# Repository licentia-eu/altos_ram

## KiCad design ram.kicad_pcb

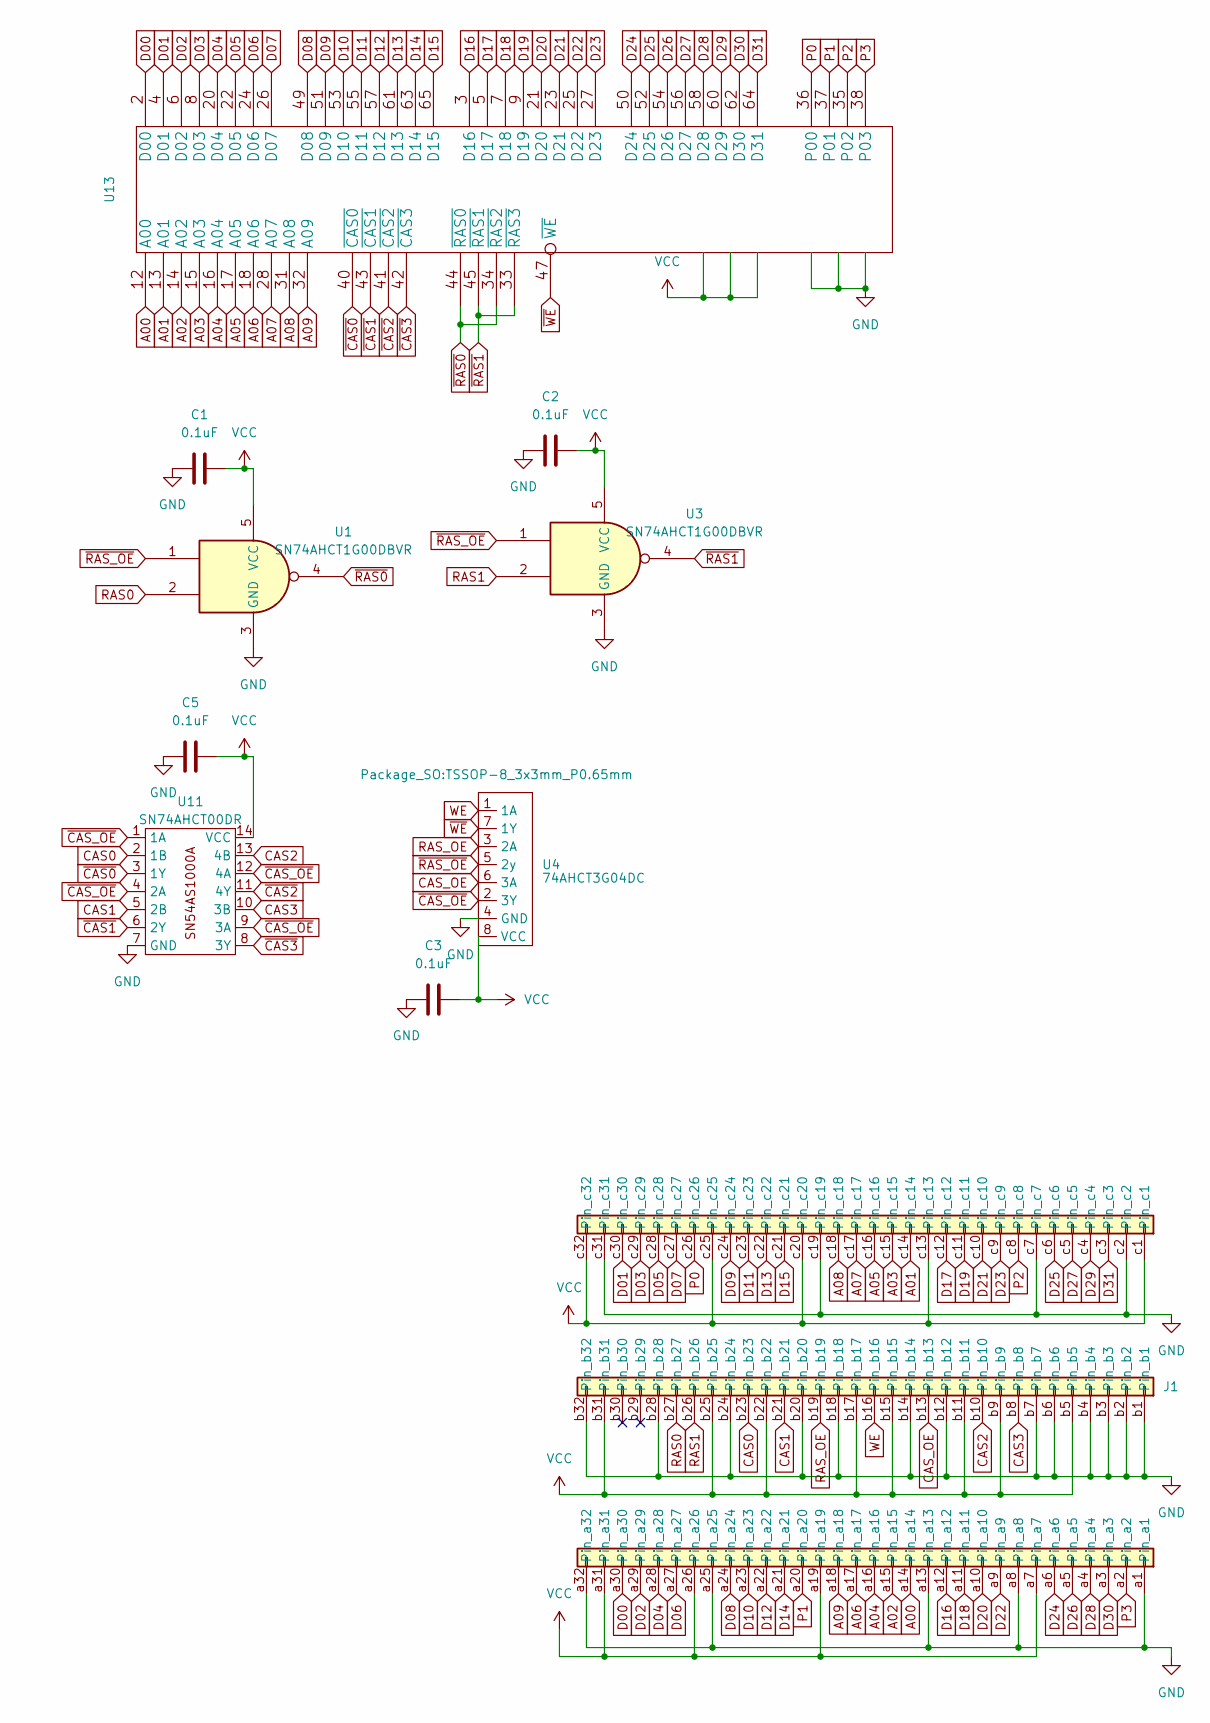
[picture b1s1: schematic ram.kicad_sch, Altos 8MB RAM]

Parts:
C1, C2, C3, C5: 0.1uF; C_1210_3225Metric
J1: DIN41612_R_3x32_Male_Horizontal_THT
U1, U3: SN74AHCT1G00DBVR; SOT-23-5
U4: 74AHCT3G04DC; TSSOP-8_3x3mm_P0.65mm
U11: SN74AHCT00DR; SSOP-14_5.3x6.2mm_P0.65mm
U13: SIM72

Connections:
A00: J1.a14, U13.12 (A00)
A01: J1.c14, U13.13 (A01)
A02: J1.a15, U13.14 (A02)
A03: J1.c15, U13.15 (A03)
A04: J1.a16, U13.16 (A04)
A05: J1.c16, U13.17 (A05)
A06: J1.a17, U13.18 (A06)
A07: J1.c17, U13.28 (A07)
A08: J1.c18, U13.31 (A08)
A09: J1.a18, U13.32 (A09)
CAS0: J1.b23, U11.2 (1B)
CAS1: J1.b21, U11.5 (2B)
CAS2: J1.b10, U11.13 (4B)
CAS3: J1.b8, U11.10 (3B)
CAS_OE: J1.b13, U4.6 (3A)
D00: J1.a30, U13.2 (D00)
D01: J1.c30, U13.4 (D01)
D02: J1.a29, U13.6 (D02)
D03: J1.c29, U13.8 (D03)
D04: J1.a28, U13.20 (D04)
D05: J1.c28, U13.22 (D05)
D06: J1.a27, U13.24 (D06)
D07: J1.c27, U13.26 (D07)
D08: J1.a24, U13.49 (D08)
D09: J1.c24, U13.51 (D09)
D10: J1.a23, U13.53 (D10)
D11: J1.c23, U13.55 (D11)
D12: J1.a22, U13.57 (D12)
D13: J1.c22, U13.61 (D13)
D14: J1.a21, U13.63 (D14)
D15: J1.c21, U13.65 (D15)
D16: J1.a12, U13.3 (D16)
D17: J1.c12, U13.5 (D17)
D18: J1.a11, U13.7 (D18)
D19: J1.c11, U13.9 (D19)
D20: J1.a10, U13.21 (D20)
D21: J1.c10, U13.23 (D21)
D22: J1.a9, U13.25 (D22)
D23: J1.c9, U13.27 (D23)
D24: J1.a6, U13.50 (D24)
D25: J1.c6, U13.52 (D25)
D26: J1.a5, U13.54 (D26)
D27: J1.c5, U13.56 (D27)
D28: J1.a4, U13.58 (D28)
D29: J1.c4, U13.60 (D29)
D30: J1.a3, U13.62 (D30)
D31: J1.c3, U13.64 (D31)
GND: C1.1, C2.1, C3.1, C5.1, J1.a1, J1.a8, J1.a13, J1.a25, J1.a32, J1.b1, J1.b2, J1.b3, J1.b4, J1.b6, J1.b7, J1.b12, J1.b14, J1.b18, J1.b20, J1.b24, J1.b28, J1.b32, J1.c2, J1.c7, J1.c19, J1.c31, U1.3 (GND), U3.3 (GND), U4.4 (GND), U11.7 (GND), U13.1 (GND), U13.39 (GND), U13.72 (GND)
P0: J1.c26, U13.36 (P00)
P1: J1.a20, U13.37 (P01)
P2: J1.c8, U13.35 (P02)
P3: J1.a2, U13.38 (P03)
RAS0: J1.b27, U1.2
RAS1: J1.b26, U3.2
RAS_OE: J1.b19, U4.3 (2A)
VCC: C1.2, C2.2, C3.2, C5.2, J1.a7, J1.a19, J1.a26, J1.a31, J1.b5, J1.b9, J1.b11, J1.b15, J1.b17, J1.b22, J1.b25, J1.b31, J1.c1, J1.c13, J1.c20, J1.c25, J1.c32, U1.5 (VCC), U3.5 (VCC), U4.8 (VCC), U11.14 (VCC), U13.10 (VCC), U13.30 (VCC), U13.59 (VCC)
WE: J1.b16, U4.1 (1A)
~CAS0: U11.3 (1Y), U13.40 (~CAS0)
~CAS1: U11.6 (2Y), U13.43 (~CAS1)
~CAS2: U11.11 (4Y), U13.41 (~CAS2)
~CAS3: U11.8 (3Y), U13.42 (~CAS3)
~CAS_OE: U4.2 (3Y), U11.1 (1A), U11.4 (2A), U11.9 (3A), U11.12 (4A)
~RAS0: U1.4, U13.34 (~RAS2), U13.44 (~RAS0)
~RAS1: U3.4, U13.33 (~RAS3), U13.45 (~RAS1)
~RAS_OE: U1.1, U3.1, U4.5 (2y)
~WE: U4.7 (1Y), U13.47 (~WE)

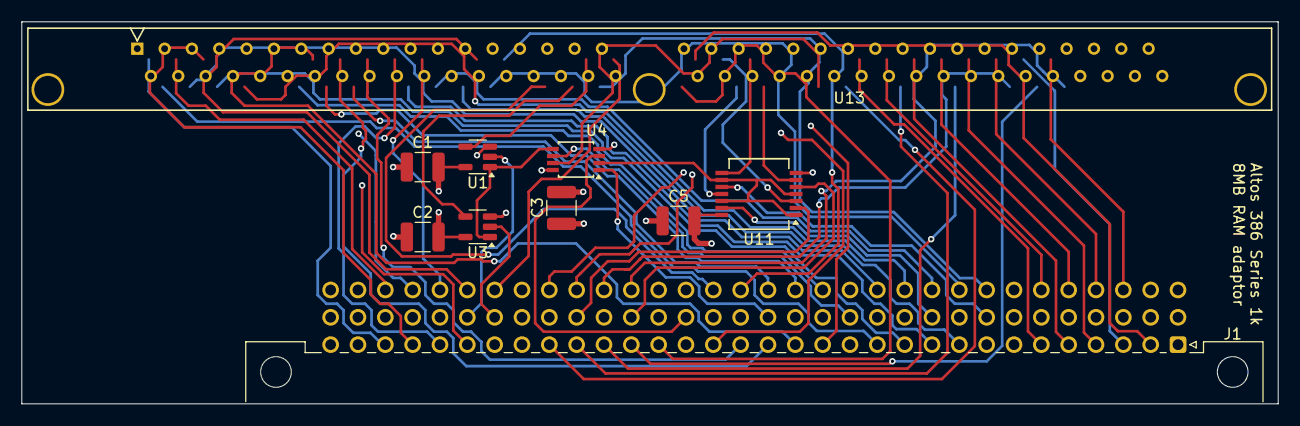
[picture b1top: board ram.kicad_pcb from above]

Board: 4 copper layers, 116.8 x 35.5 mm, 10 parts (0 on the bottom side), 66 nets.

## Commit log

2024-09-12 Initial import
2024-09-13 Fixed WE pin (it's on B16 not B17)
2024-09-13 Identify the remaining connector pins
2024-09-14 Fixed all CAS & RAS pins
2024-09-14 WIP: 8MB 72 pin SIMM to Altos 8MB RAM module
2024-09-26 8MB 72 pin SIMM to Altos 8MB RAM module
2024-09-26 Made a 4 layer PCB, and also smaller, routing done.
2024-09-27 Add ICs descriptions
    Cook first PCB iteration.
2024-10-07 Fix simm position
